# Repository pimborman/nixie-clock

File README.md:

# Description

This repository contains the design files of my own nixie clock. The last version is hosted on my [Github Page](https://pimborman.github.io/nixie-clock).

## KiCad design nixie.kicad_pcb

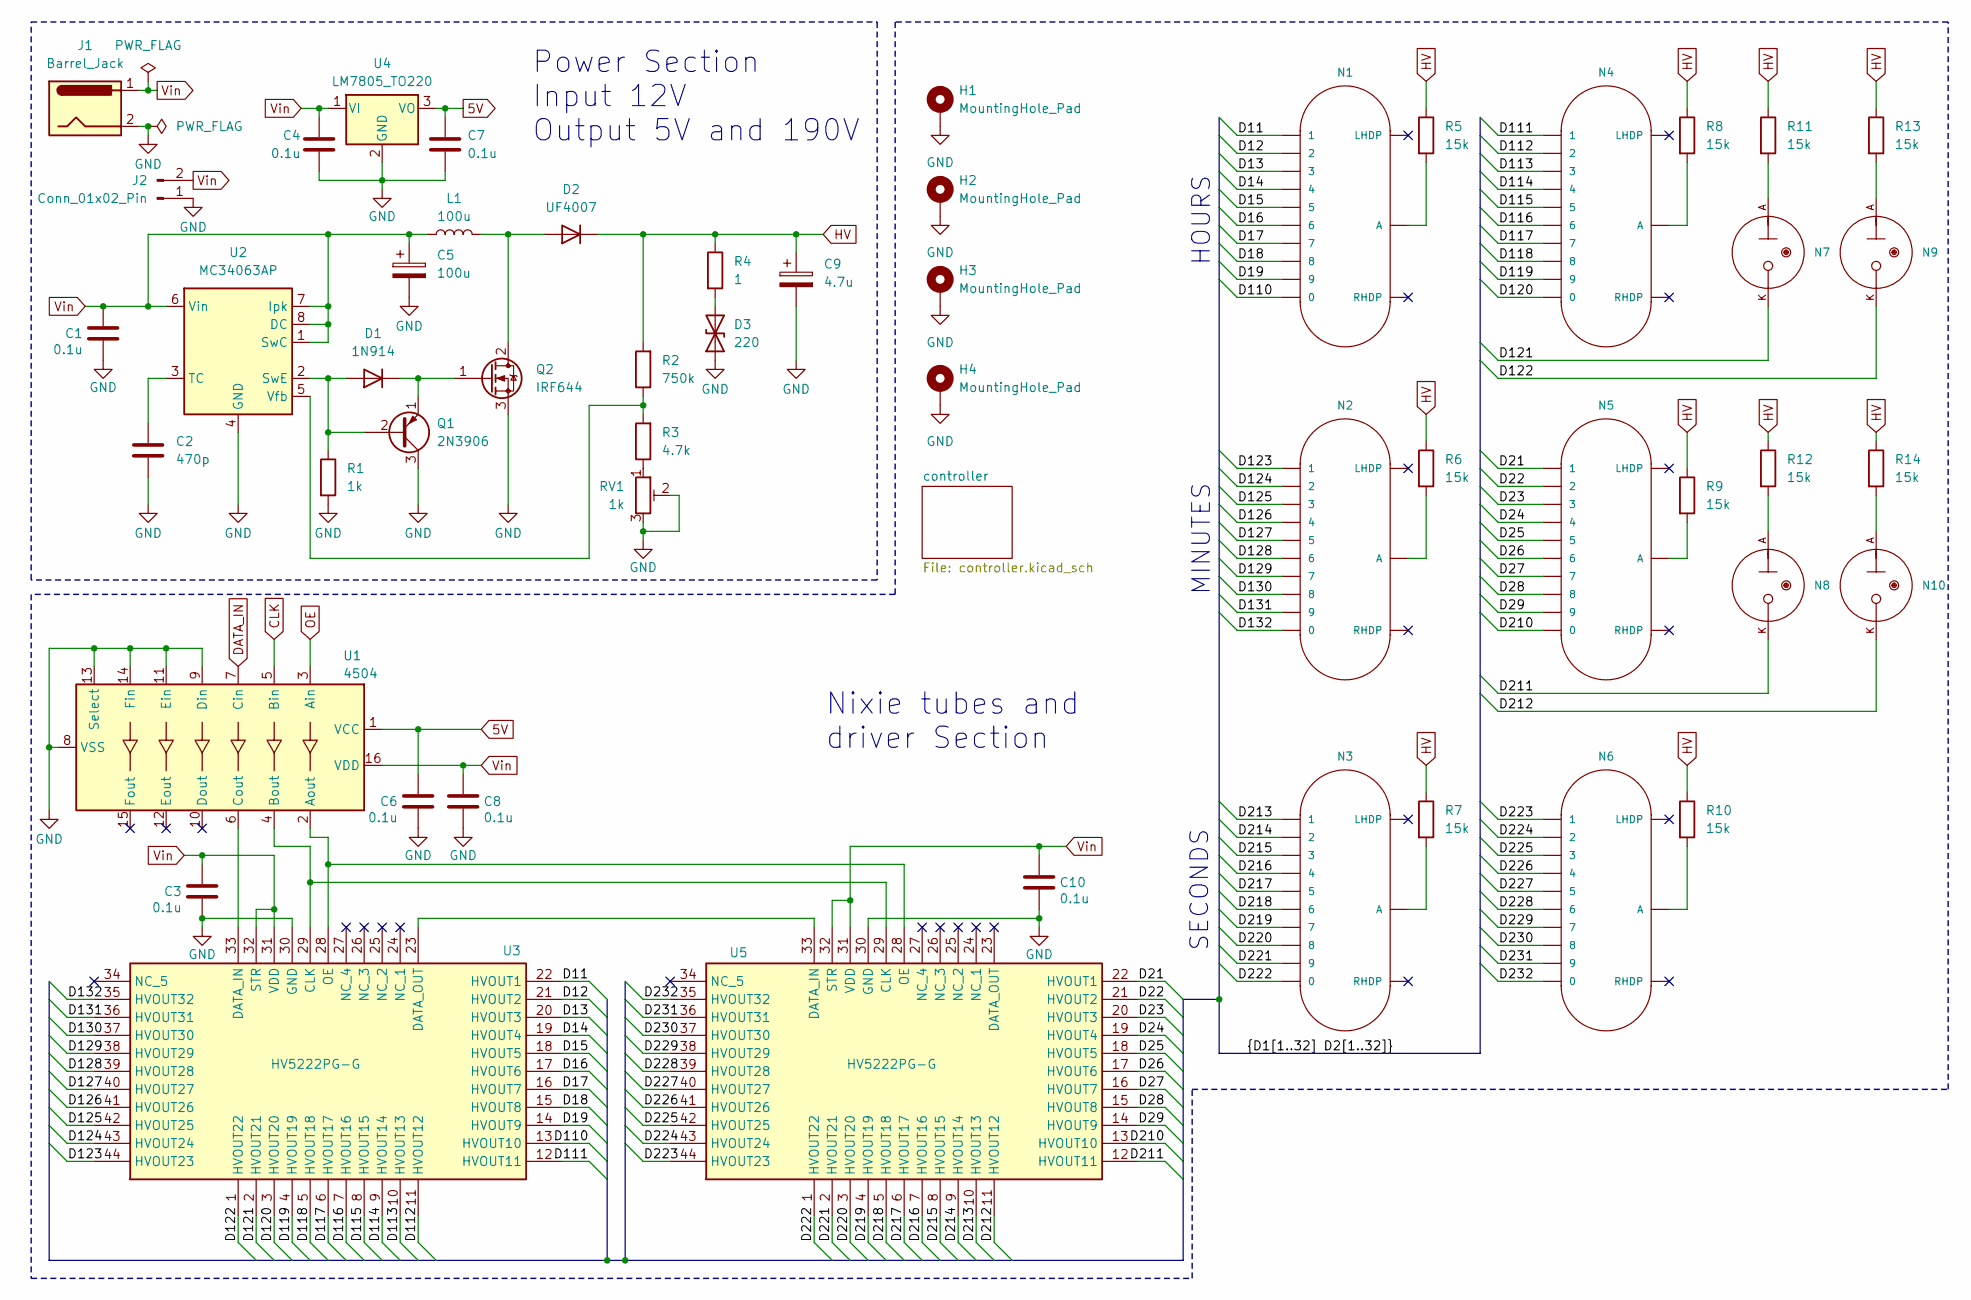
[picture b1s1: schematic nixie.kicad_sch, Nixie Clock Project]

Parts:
C1, C3, C4, C6, C7, C8, C10: 0.1u; C_Disc_D4.7mm_W2.5mm_P5.00mm
C2: 470p; C_Disc_D3.8mm_W2.6mm_P2.50mm
C5: 100u; CP_Radial_D6.3mm_P2.50mm
C9: 4.7u; CP_Radial_D8.0mm_P3.50mm
D1: 1N914; D_DO-35_SOD27_P7.62mm_Horizontal
D2: UF4007; D_DO-41_SOD81_P7.62mm_Horizontal
D3: 220; D_DO-15_P10.16mm_Horizontal
H1, H2, H3, H4: MountingHole_Pad; MountingHole_3.2mm_M3_Pad_Via
J1: Barrel_Jack; TerminalBlock_Phoenix_MKDS-1,5-2-5.08_1x02_P5.08mm_Horizont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
J2: Conn_01x02_Pin; PinHeader_1x02_P2.54mm_Vertical
L1: 100u; L_Radial_D8.7mm_P5.00mm_Fastron_07HCP
N1, N2, N3, N4, N5, N6: IN-14; nixies-us-IN-14
N7, N8, N9, N10: IN-3; nixies-us-IN-3
Q1: 2N3906; TO-92_Inline
Q2: IRF644; TO-220-3_Horizontal_TabDown
R1: 1k; R_Axial_DIN0207_L6.3mm_D2.5mm_P7.62mm_Horizontal
R2: 750k; R_Axial_DIN0207_L6.3mm_D2.5mm_P7.62mm_Horizontal
R3: 4.7k; R_Axial_DIN0207_L6.3mm_D2.5mm_P7.62mm_Horizontal
R4: 1; R_Axial_DIN0207_L6.3mm_D2.5mm_P7.62mm_Horizontal
R5, R6, R7, R8, R9, R10, R11, R12, R13, R14: 15k; R_Axial_DIN0207_L6.3mm_D2.5mm_P7.62mm_Horizontal
RV1: 1k; Potentiometer_Bourns_3306P_Vertical
U1: 4504; DIP-16_W7.62mm
U2: MC34063AP; DIP-8_W7.62mm
U3, U5: HV5222PG-G; PQFP-44_10x10mm_P0.8mm; Manufacturer_Part_Number HV5222PG-G; Mouser Part Number 689-HV5222PG-G
U4: LM7805_TO220; TO-220-3_Horizontal_TabDown

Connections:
5V: C6.1, C7.1, U1.1 (VCC), U4.3 (VO); also elsewhere on the board
/D11: N1.1, U3.22 (HVOUT1)
/D12: N1.2, U3.21 (HVOUT2)
/D13: N1.3, U3.20 (HVOUT3)
/D14: N1.4, U3.19 (HVOUT4)
/D15: N1.5, U3.18 (HVOUT5)
/D16: N1.6, U3.17 (HVOUT6)
/D17: N1.7, U3.16 (HVOUT7)
/D18: N1.8, U3.15 (HVOUT8)
/D19: N1.9, U3.14 (HVOUT9)
/D21: N5.1, U5.22 (HVOUT1)
/D22: N5.2, U5.21 (HVOUT2)
/D23: N5.3, U5.20 (HVOUT3)
/D24: N5.4, U5.19 (HVOUT4)
/D25: N5.5, U5.18 (HVOUT5)
/D26: N5.6, U5.17 (HVOUT6)
/D27: N5.7, U5.16 (HVOUT7)
/D28: N5.8, U5.15 (HVOUT8)
/D29: N5.9, U5.14 (HVOUT9)
/D110: N1.0, U3.13 (HVOUT10)
/D111: N4.1, U3.12 (HVOUT11)
/D112: N4.2, U3.11 (HVOUT12)
/D113: N4.3, U3.10 (HVOUT13)
/D114: N4.4, U3.9 (HVOUT14)
/D115: N4.5, U3.8 (HVOUT15)
/D116: N4.6, U3.7 (HVOUT16)
/D117: N4.7, U3.6 (HVOUT17)
/D118: N4.8, U3.5 (HVOUT18)
/D119: N4.9, U3.4 (HVOUT19)
/D120: N4.0, U3.3 (HVOUT20)
/D121: N7.K, U3.2 (HVOUT21)
/D122: N9.K, U3.1 (HVOUT22)
/D123: N2.1, U3.44 (HVOUT23)
/D124: N2.2, U3.43 (HVOUT24)
/D125: N2.3, U3.42 (HVOUT25)
/D126: N2.4, U3.41 (HVOUT26)
/D127: N2.5, U3.40 (HVOUT27)
/D128: N2.6, U3.39 (HVOUT28)
/D129: N2.7, U3.38 (HVOUT29)
/D130: N2.8, U3.37 (HVOUT30)
/D131: N2.9, U3.36 (HVOUT31)
/D132: N2.0, U3.35 (HVOUT32)
/D210: N5.0, U5.13 (HVOUT10)
/D211: N8.K, U5.12 (HVOUT11)
/D212: N10.K, U5.11 (HVOUT12)
/D213: N3.1, U5.10 (HVOUT13)
/D214: N3.2, U5.9 (HVOUT14)
/D215: N3.3, U5.8 (HVOUT15)
/D216: N3.4, U5.7 (HVOUT16)
/D217: N3.5, U5.6 (HVOUT17)
/D218: N3.6, U5.5 (HVOUT18)
/D219: N3.7, U5.4 (HVOUT19)
/D220: N3.8, U5.3 (HVOUT20)
/D221: N3.9, U5.2 (HVOUT21)
/D222: N3.0, U5.1 (HVOUT22)
/D223: N6.1, U5.44 (HVOUT23)
/D224: N6.2, U5.43 (HVOUT24)
/D225: N6.3, U5.42 (HVOUT25)
/D226: N6.4, U5.41 (HVOUT26)
/D227: N6.5, U5.40 (HVOUT27)
/D228: N6.6, U5.39 (HVOUT28)
/D229: N6.7, U5.38 (HVOUT29)
/D230: N6.8, U5.37 (HVOUT30)
/D231: N6.9, U5.36 (HVOUT31)
/D232: N6.0, U5.35 (HVOUT32)
CLK: U1.5 (Bin); also elsewhere on the board
DATA_IN: U1.7 (Cin); also elsewhere on the board
GND: C1.2, C2.2, C3.2, C4.2, C5.2, C6.2, C7.2, C8.2, C9.2, C10.2, D3.1 (A1), H1.1, H2.1, H3.1, H4.1, J1.2, J2.1, Q1.3 (C), Q2.3 (S), R1.2, RV1.2, RV1.3, U1.8 (VSS), U1.9 (Din), U1.11 (Ein), U1.13 (Select), U1.14 (Fin), U2.4 (GND), U3.30 (GND), U4.2 (GND), U5.30 (GND); also elsewhere on the board
HV: C9.1, D2.1 (K), R2.2, R4.1, R5.1, R6.1, R7.1, R8.1, R9.1, R10.1, R11.1, R12.1, R13.1, R14.1
unnamed: D1.2 (A), Q1.2 (B), R1.1, U2.2 (SwE)
unnamed: D1.1 (K), Q1.1 (E), Q2.1 (G)
unnamed: D2.2 (A), L1.2, Q2.2 (D)
unnamed: D3.2 (A2), R4.2
unnamed: N1.A, R5.2
unnamed: N2.A, R6.2
unnamed: N3.A, R7.2
unnamed: N4.A, R8.2
unnamed: N5.A, R9.2
unnamed: N6.A, R10.2
unnamed: N7.A, R11.2
unnamed: N8.A, R12.2
unnamed: N9.A, R13.2
unnamed: N10.A, R14.2
unnamed: R3.1, RV1.1
unnamed: U1.2 (Aout), U3.28 (OE), U5.28 (OE)
unnamed: U1.4 (Bout), U3.29 (CLK), U5.29 (CLK)
unnamed: U1.6 (Cout), U3.33 (DATA_IN)
unnamed: C2.1, U2.3 (TC)
unnamed: R2.1, R3.2, U2.5 (Vfb)
unnamed: U3.23 (DATA_OUT), U5.33 (DATA_IN)
OE: U1.3 (Ain); also elsewhere on the board
Vin: C1.1, C3.1, C4.1, C5.1, C8.1, C10.1, J1.1, J2.2, L1.1, U1.16 (VDD), U2.1 (SwC), U2.6 (Vin), U2.7 (Ipk), U2.8 (DC), U3.31 (VDD), U3.32 (STR), U4.1 (VI), U5.31 (VDD), U5.32 (STR)

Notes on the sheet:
MINUTES
SECONDS
Power Section Input 12V Output 5V and 190V
HOURS
Nixie tubes and driver Section

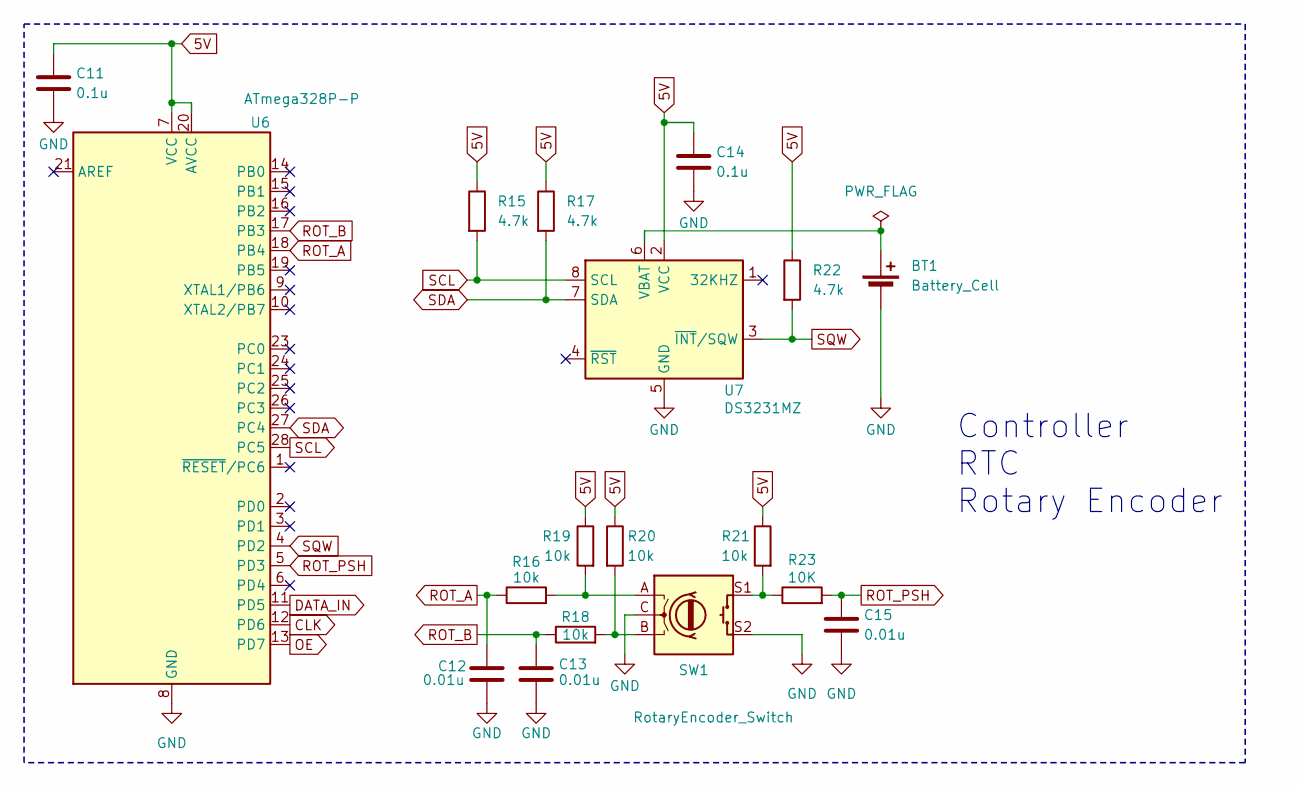
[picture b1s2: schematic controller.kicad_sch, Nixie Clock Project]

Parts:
BT1: Battery_Cell; BH-80B-1
C11, C14: 0.1u; C_Disc_D4.7mm_W2.5mm_P5.00mm
C12, C13, C15: 0.01u; C_Disc_D4.7mm_W2.5mm_P5.00mm
R15, R17, R22: 4.7k; R_Axial_DIN0207_L6.3mm_D2.5mm_P7.62mm_Horizontal
R16, R18, R19, R20, R21: 10k; R_Axial_DIN0207_L6.3mm_D2.5mm_P7.62mm_Horizontal
R23: 10K; R_Axial_DIN0207_L6.3mm_D2.5mm_P7.62mm_Horizontal
SW1: RotaryEncoder_Switch; PEC11H4020FS0016
U6: ATmega328P-P; DIP-28_W7.62mm
U7: DS3231MZ; SOIC-8_3.9x4.9mm_P1.27mm

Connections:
5V: C11.1, C14.1, R15.1, R17.1, R19.1, R20.1, R21.1, R22.1, U6.7 (VCC), U6.20 (AVCC), U7.2 (VCC); also elsewhere on the board
CLK: U6.12 (PD6); also elsewhere on the board
DATA_IN: U6.11 (PD5); also elsewhere on the board
GND: BT1.2 (-), C11.2, C12.2, C13.2, C14.2, C15.2, SW1.C, SW1.S2, U6.8 (GND), U6.22 (GND), U7.5 (GND); also elsewhere on the board
unnamed: BT1.1 (+), U7.6 (VBAT)
unnamed: R16.2, R19.2, SW1.A
unnamed: R18.2, R20.2, SW1.B
unnamed: R21.2, R23.1, SW1.S1
OE: U6.13 (PD7); also elsewhere on the board
ROT_A: C12.1, R16.1, U6.18 (PB4)
ROT_B: C13.1, R18.1, U6.17 (PB3)
ROT_PSH: C15.1, R23.2, U6.5 (PD3)
SCL: R15.2, U6.28 (PC5), U7.8 (SCL)
SDA: R17.2, U6.27 (PC4), U7.7 (SDA)
SQW: R22.2, U6.4 (PD2), U7.3 (~INT/SQW)

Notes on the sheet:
Controller RTC Rotary Encoder

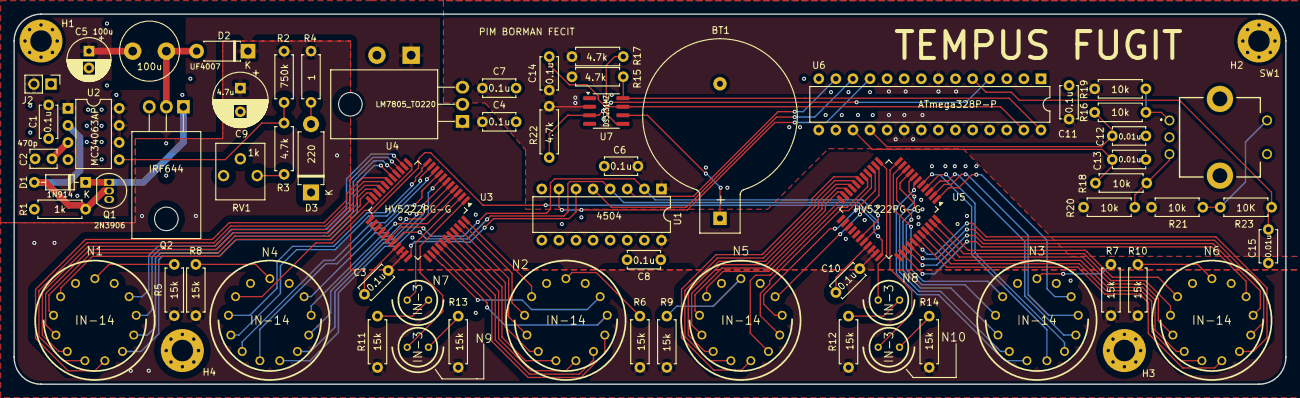
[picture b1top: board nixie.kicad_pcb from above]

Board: 4 copper layers, 189.0 x 55.0 mm, 70 parts (1 on the bottom side), 102 nets.

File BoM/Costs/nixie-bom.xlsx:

|  | KiBot Bill of Materials
 |  | Schematic: | nixie | Component Groups: | 30
 |  | Variant: | default | Component Count: | 66 (3 SMD/ 63 THT)
 |  | Revision: | v1.1 | Fitted Components: | 66 (3 SMD/ 63 THT)
 |  | Date: | 2024-10-13 | Number of PCBs: | 1
 |  | KiCad Version: | 8.0.4+1 | Total Components: | 66
Row | Description | Part | References | Value | Footprint | Quantity Per PCB | Status | Datasheet | Sim.Device | Sim.Pins | Height | Manufacturer_Name | Manufacturer_Part_Number | Mouser Part Number | Mouser Price/Stock | Arrow Part Number | Arrow Price/Stock
1 |  | Battery_Cell | BT1 | Battery_Cell | BH-80B-1 | 1 |  | ~
2 |  | C | C2 | 470p | C_Disc_D3.8mm_W2.6mm_P2.50mm | 1 |  | ~
3 |  | C | C12 C13 C15 | 0.01u | C_Disc_D4.7mm_W2.5mm_P5.00mm | 3 |  | ~
4 |  | C | C1 C3 C4 C6 C7 C8 C10 C11 C14 | 0.1u | C_Disc_D4.7mm_W2.5mm_P5.00mm | 9 |  | ~
5 |  | C_Polarized | C9 | 4.7u | CP_Radial_D8.0mm_P3.50mm | 1 |  | ~
6 |  | C_Polarized | C5 | 100u | CP_Radial_D6.3mm_P2.50mm | 1 |  | ~
7 |  | 1N914 | D1 | 1N914 | D_DO-35_SOD27_P7.62mm_Horizontal | 1 |  | http://www.vishay.com/docs/85622/1n914.pdf | D | 1=K 2=A
8 |  | D_TVS | D3 | 220 | D_DO-15_P10.16mm_Horizontal | 1 |  | https://nl.mouser.com/datasheet/2/389/p6ke12ca-3078729.pdf
9 |  | D | D2 | UF4007 | D_DO-41_SOD81_P7.62mm_Horizontal | 1 |  | ~ | D | 1=K 2=A
10 |  | Barrel_Jack | J1 | Barrel_Jack | TerminalBlock_Phoenix_MKDS-1,5-2-5.08_1x02_P5.08mm_Horizontal | 1 |  | ~
11 |  | Conn_01x02_Pin | J2 | Conn_01x02_Pin | PinHeader_1x02_P2.54mm_Vertical | 1 |  | ~
12 |  | L | L1 | 100u | L_Radial_D8.7mm_P5.00mm_Fastron_07HCP | 1 |  | ~
13 |  | IN-14 | N1 N2 N3 N4 N5 N6 | IN-14 | nixies-us-IN-14 | 6
14 |  | IN-3 | N7 N8 N9 N10 | IN-3 | nixies-us-IN-3 | 4
15 |  | 2N3906 | Q1 | 2N3906 | TO-92_Inline | 1 |  | https://www.onsemi.com/pub/Collateral/2N3906-D.PDF
16 |  | Q_NMOS_GDS | Q2 | IRF644 | TO-220-3_Horizontal_TabDown | 1 |  | https://www.vishay.com/docs/91039/91039.pdf
17 |  | R | R1 | R | R_Axial_DIN0207_L6.3mm_D2.5mm_P7.62mm_Horizontal | 1 |  | ~
18 |  | R | R4 | 1 | R_Axial_DIN0207_L6.3mm_D2.5mm_P7.62mm_Horizontal | 1 |  | ~
19 |  | R | R3 R15 R17 R22 | 4.7k | R_Axial_DIN0207_L6.3mm_D2.5mm_P7.62mm_Horizontal | 4 |  | ~
20 |  | R | R16 R18 R19 R20 R21 R23 | 10k | R_Axial_DIN0207_L6.3mm_D2.5mm_P7.62mm_Horizontal | 6 |  | ~
21 |  | R | R5 R6 R7 R8 R9 R10 R11 R12 R13 R14 | 15k | R_Axial_DIN0207_L6.3mm_D2.5mm_P7.62mm_Horizontal | 10 |  | ~
22 |  | R | R2 | 800k | R_Axial_DIN0207_L6.3mm_D2.5mm_P7.62mm_Horizontal | 1 |  | ~
23 |  | R_Potentiometer_Trim | RV1 | 1k | Potentiometer_Bourns_3306P_Vertical | 1 |  | ~
24 |  | RotaryEncoder_Switch | SW1 | RotaryEncoder_Switch | PEC11H4020FS0016 | 1 |  | ~
25 |  | 4504 | U1 | 4504 | DIP-16_W7.62mm | 1 |  | http://www.ti.com/lit/ds/symlink/cd4504b.pdf
26 |  | ATmega328P-P | U6 | ATmega328P-P | DIP-28_W7.62mm | 1 |  | http://ww1.microchip.com/downloads/en/DeviceDoc/ATmega328_P%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
27 |  | DS3231MZ | U7 | DS3231MZ | SOIC-8_3.9x4.9mm_P1.27mm | 1 |  | http://datasheets.maximintegrated.com/en/ds/DS3231M.pdf
28 |  | HV5222PG-G | U3 U5 | HV5222PG-G | PQFP-44_10x10mm_P0.8mm | 2 |  | http://www.microchip.com/mymicrochip/filehandler.aspx?ddocna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 |  |  | 2.35 | Microchip | HV5222PG-G | 689-HV5222PG-G | https://www.mouser.co.uk/ProductDetail/Microchip-Technology/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 | HV5222PG-G | https://www.arrow.com/en/products/hv5222pg-g/microchip-technology
29 |  | LM7805_TO220 | U4 | LM7805_TO220 | TO-220-3_Horizontal_TabDown | 1 |  | https://www.onsemi.cn/PowerSolutions/document/MC7800-D.PDF
30 |  | MC34063AP | U2 | MC34063AP | DIP-8_W7.62mm | 1 |  | http://www.onsemi.com/pub_link/Collateral/MC34063A-D.PDF

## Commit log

2024-08-10 initialized nixie repo
2024-08-10 added smps
2024-08-10 updated power
2024-08-10 stub with nixies and drivers
2024-08-10 connected nixie tubes, drivers, and level shifting
2024-08-10 added controller stub
2024-09-16 updated controller part
2024-09-17 added filter caps and rc debounce filter for rotary encoder
2024-09-21 added footprints
2024-09-23 first attempt at pcb layout
2024-09-28 pcb layout updated
2024-09-29 pcb layout update
2024-10-03 thicker smps traces
2024-10-03 added a few stitching HV vias
2024-10-05 added kibot yaml
2024-10-05 remapped 3d models to in-project folder
2024-10-05 removed files from gh-pages
2024-10-05 Deploying to gh-pages from @ pimborman/nixie-clock@6356c84ed416c898bfaab0297203c465fa5d6b48 🚀
2024-10-06 Deploying to gh-pages from @ pimborman/nixie-clock@f2f99fc9c055b6a24ea9afff4494f699b42b19b0 🚀
2024-10-10 added docker development container, kibot config for schematic only generation, github action updates
2024-10-10 automatic date/version control
2024-10-10 moved kibot yml to .kibot folder and added pcb workflow
2024-10-13 kibot yaml updates and make default variables empty in the project file
2024-10-13 Deploying to gh-pages from @ pimborman/nixie-clock@2eff76f5edadb4e0f35f27e81fa3de142b84cbdf 🚀
2024-10-13 added 3D model, added missing component values, improved interactive bom
2024-10-13 3D fix
2024-10-13 Deploying to gh-pages from @ pimborman/nixie-clock@de780db2857f2b30e7a47e9d26594c67cc7b3d3c 🚀
2024-10-14 updated component values
2024-10-23 connect scl sda to correct pins
